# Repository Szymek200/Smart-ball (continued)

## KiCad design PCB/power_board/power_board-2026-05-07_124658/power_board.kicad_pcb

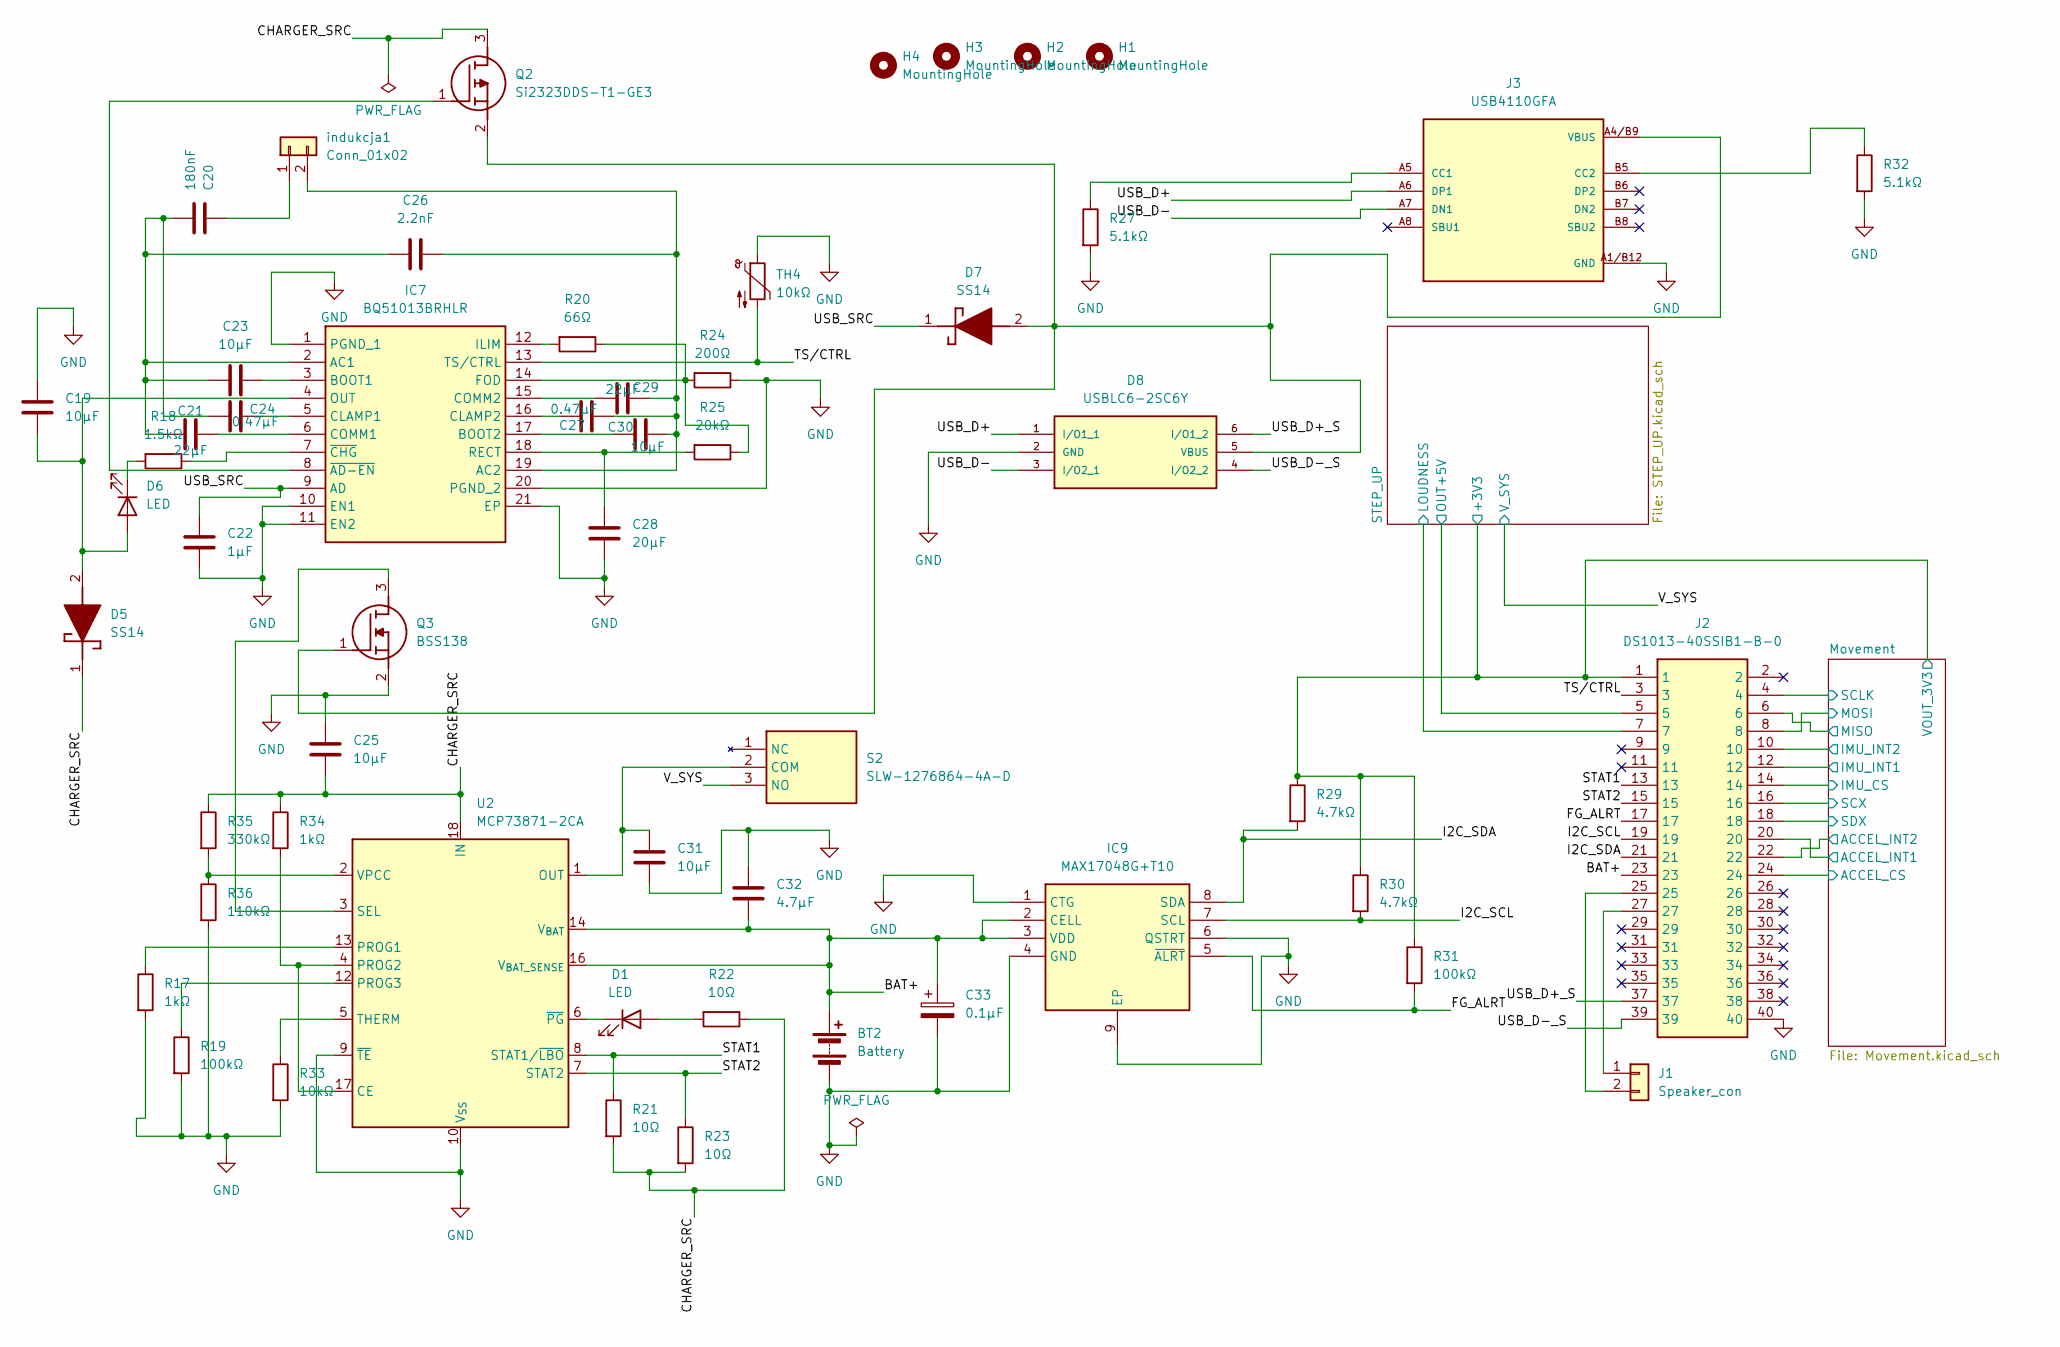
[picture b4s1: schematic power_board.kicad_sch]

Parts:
BT2: Battery; SolderWire-0.75sqmm_1x02_P4.8mm_D1.25mm_OD2.3mm
C19, C23, C25, C30, C31: 10µF; CP_EIA-3216-18_Kemet-A
C20: 180nF; CP_EIA-3216-18_Kemet-A
C21, C29: 22µF; CP_EIA-3216-18_Kemet-A
C22: 1µF; CP_EIA-3216-18_Kemet-A
C24, C27: 0.47µF; CP_EIA-3216-18_Kemet-A
C26: 2.2nF; CP_EIA-3216-18_Kemet-A
C28: 20µF; CP_EIA-3216-18_Kemet-A
C32: 4.7µF; CP_EIA-3216-18_Kemet-A
C33: 0.1µF; CP_EIA-3216-18_Kemet-A
D1, D6: LED; LED_0603_1608Metric
D5, D7: SS14; DIOM5227X270N; Mouser Part Number 512-SS14
D8: USBLC6-2SC6Y; SOT95P280X145-6N; MOUSER_PART_NUMBER 511-USBLC6-2SC6Y
H1, H2, H3, H4: MountingHole; MountingHole_3.2mm_M3_Pad_Via
IC7: BQ51013BRHLR; BQ51050BRHLR; Mouser Part Number 595-BQ51013BRHLR
IC9: MAX17048G+T10; SON50P200X200X80-9N-D; Mouser Part Number 700-MAX17048G+T10
J1: Speaker_con; PinHeader_1x02_P2.54mm_Vertical
J2: DS1013-40SSIB1-B-0; DS101340SSIB1B0; Manufacturer_Part_Number DS1013-40SSIB1-B-0
J3: USB4110GFA; GCT_USB4110GFA
Q2: Si2323DDS-T1-GE3; SOT95P237X112-3N; Mouser Part Number 78-SI2323DDS-T1-GE3
Q3: BSS138; SOT95P240X120-3N; Mouser Part Number 512-BSS138
R17, R34: 1kΩ; R_0603_1608Metric
R18: 1.5kΩ; R_0603_1608Metric
R19, R31: 100kΩ; R_0603_1608Metric
R20: 66Ω; R_0603_1608Metric
R21, R22, R23: 10Ω; R_0603_1608Metric
R24: 200Ω; R_0603_1608Metric
R25: 20kΩ; R_0603_1608Metric
R27, R32: 5.1kΩ; R_0603_1608Metric
R29, R30: 4.7kΩ; R_0603_1608Metric
R33: 10kΩ; R_0603_1608Metric
R35: 330kΩ; R_0603_1608Metric
R36: 110kΩ; R_0603_1608Metric
S2: SLW-1276864-4A-D; SLW12768644AD; Mouser Part Number 179-SLW-1276864-4A-D
TH4: 10kΩ; R_0603_1608Metric
U2: MCP73871-2CA; QFN-20-1EP_4x4mm_P0.5mm_EP2.5x2.5mm
indukcja1: Conn_01x02; PinHeader_1x02_P2.54mm_Vertical

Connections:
/BAT+: BT2.1 (+), C32.2, C33.1, IC9.2 (CELL), IC9.3 (VDD), J2.23, U2.14 (V_{BAT}), U2.15 (V_{BAT}), U2.16 (V_{BAT_SENSE})
/CHARGER_SRC: C25.2, D5.1 (K), Q2.3 (D), R21.2, R22.1, R23.2, R34.1, R35.1, U2.18 (IN), U2.19 (IN)
/FG_ALRT: IC9.5 (~ALRT), J2.17, R31.2
/I2C_SCL: IC9.7 (SCL), J2.19, R30.2
/I2C_SDA: IC9.8 (SDA), J2.21, R29.2
/Movement/ACCEL_CS: J2.24; also elsewhere on the board
/Movement/ACCEL_INT1: J2.20; also elsewhere on the board
/Movement/ACCEL_INT2: J2.22; also elsewhere on the board
/Movement/IMU_CS: J2.14; also elsewhere on the board
/Movement/IMU_INT1: J2.12; also elsewhere on the board
/Movement/IMU_INT2: J2.10; also elsewhere on the board
/Movement/MISO: J2.6; also elsewhere on the board
/Movement/MOSI: J2.8; also elsewhere on the board
/Movement/SCLK: J2.4; also elsewhere on the board
/Movement/SCX: J2.16; also elsewhere on the board
/Movement/SDX: J2.18; also elsewhere on the board
/Movement/VOUT_3V3: J2.1, R29.1, R30.1, R31.1; also elsewhere on the board
/STAT1: J2.13, R21.1, U2.8 (STAT1/~LBO)
/STAT2: J2.15, R23.1, U2.7 (STAT2)
/STEP_UP/LOUDNESS: J2.7; also elsewhere on the board
/STEP_UP/OUT+5V: J2.5; also elsewhere on the board
/TS/CTRL: IC7.13 (TS/CTRL), J2.3, TH4.2
/USB_D+: D8.1 (I/O1_1), J3.A6 (DP1)
/USB_D+_S: D8.6 (I/O1_2), J2.37
/USB_D-: D8.3 (I/O2_1), J3.A7 (DN1)
/USB_D-_S: D8.4 (I/O2_2), J2.39
/USB_SRC: C22.1, D7.1 (K), IC7.9 (AD)
/V_SYS: S2.3 (NO); also elsewhere on the board
GND: BT2.2 (-), C19.2, C22.2, C25.1, C28.2, C31.2, C32.1, C33.2, D8.2 (GND), IC7.1 (PGND_1), IC7.10 (EN1), IC7.11 (EN2), IC7.20 (PGND_2), IC7.21 (EP), IC9.1 (CTG), IC9.4 (GND), IC9.6 (QSTRT), IC9.9 (EP), J2.40, J3.A1/B12 (GND), J3.B1/A12 (GND), J3.S1 (GND), J3.S2 (GND), J3.S3 (GND), J3.S4 (GND), Q3.2 (S), R17.2, R19.2, R24.1, R27.2, R32.2, R33.2, R36.2, TH4.1, U2.9 (~TE), U2.10 (V_{SS}), U2.11 (V_{SS}), U2.21 (V_{SS}); also elsewhere on the board
unnamed: D1.2 (A), R22.2
unnamed: D1.1 (K), U2.6 (~PG)
unnamed: C19.1, D5.2 (A), D6.2 (A), IC7.4 (OUT)
unnamed: D6.1 (K), R18.2
unnamed: C20.2, C21.2, C23.2, C24.2, C26.2, IC7.2 (AC1)
unnamed: C26.1, C27.1, C29.1, C30.1, IC7.19 (AC2), indukcja1.2
unnamed: C23.1, IC7.3 (BOOT1)
unnamed: C30.2, IC7.17 (BOOT2)
unnamed: C24.1, IC7.5 (CLAMP1)
unnamed: C27.2, IC7.16 (CLAMP2)
unnamed: C21.1, IC7.6 (COMM1)
unnamed: C29.2, IC7.15 (COMM2)
unnamed: IC7.14 (FOD), R20.1, R24.2, R25.1
unnamed: IC7.12 (ILIM), R20.2
unnamed: C28.1, IC7.18 (RECT), R25.2
unnamed: IC7.8 (~AD-EN), Q2.1 (G)
unnamed: IC7.7 (~CHG), R18.1
unnamed: J1.1, J2.27
unnamed: J1.2, J2.25
unnamed: J3.A5 (CC1), R27.1
unnamed: J3.B5 (CC2), R32.1
unnamed: Q3.3 (D), U2.3 (SEL)
unnamed: C31.1, S2.2 (COM), U2.1 (OUT), U2.20 (OUT)
unnamed: R34.2, U2.4 (PROG2), U2.17 (CE)
unnamed: R17.1, U2.13 (PROG1)
unnamed: R19.1, U2.12 (PROG3)
unnamed: R33.1, U2.5 (THERM)
unnamed: R35.2, R36.1, U2.2 (VPCC)
unnamed: C20.1, indukcja1.1
VBUS: D7.2 (A), D8.5 (VBUS), J3.A4/B9 (VBUS), J3.B4/A9 (VBUS), Q2.2 (S), Q3.1 (G)

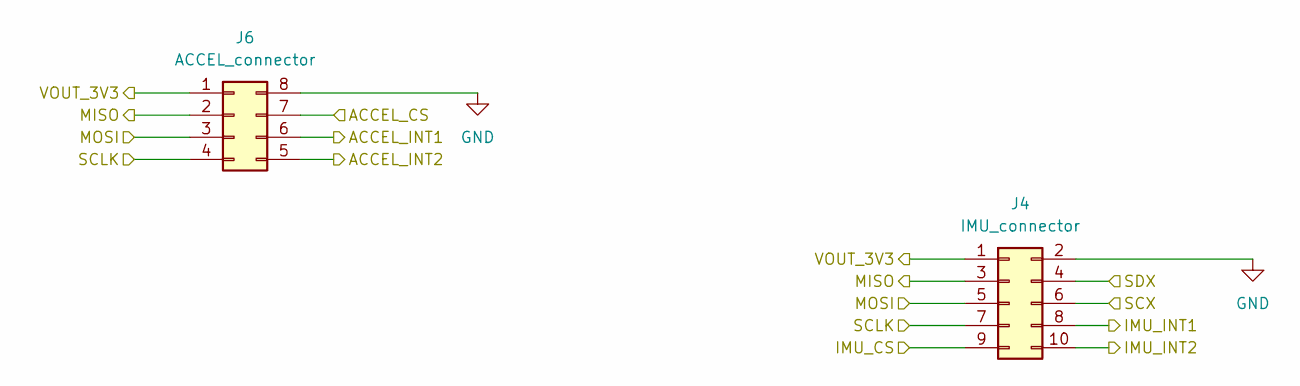
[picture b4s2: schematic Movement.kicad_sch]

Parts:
J4: IMU_connector; PinHeader_2x05_P2.54mm_Vertical
J6: ACCEL_connector; PinHeader_2x04_P2.54mm_Vertical

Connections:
/Movement/ACCEL_CS: J6.7; also elsewhere on the board
/Movement/ACCEL_INT1: J6.6; also elsewhere on the board
/Movement/ACCEL_INT2: J6.5; also elsewhere on the board
/Movement/IMU_CS: J4.9; also elsewhere on the board
/Movement/IMU_INT1: J4.8; also elsewhere on the board
/Movement/IMU_INT2: J4.10; also elsewhere on the board
/Movement/MISO: J4.3, J6.2; also elsewhere on the board
/Movement/MOSI: J4.5, J6.3; also elsewhere on the board
/Movement/SCLK: J4.7, J6.4; also elsewhere on the board
/Movement/SCX: J4.6; also elsewhere on the board
/Movement/SDX: J4.4; also elsewhere on the board
/Movement/VOUT_3V3: J4.1, J6.1; also elsewhere on the board
GND: J4.2, J6.8; also elsewhere on the board

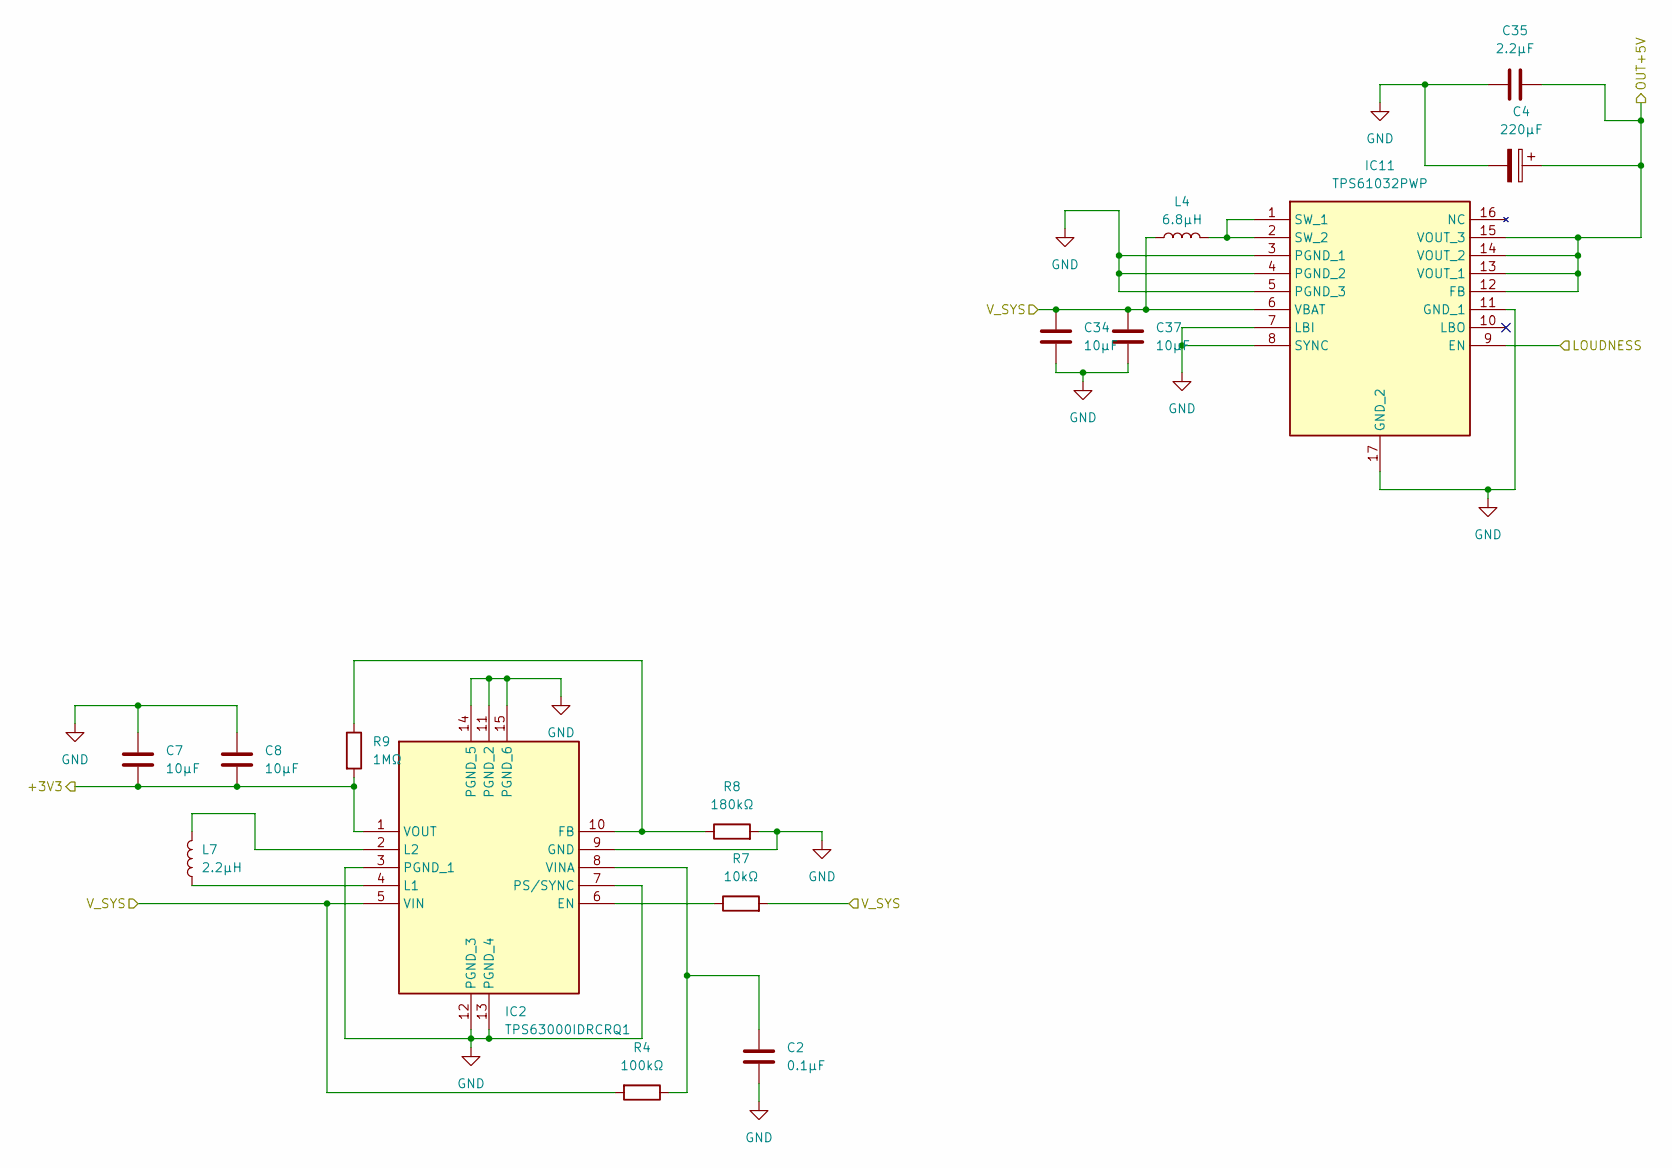
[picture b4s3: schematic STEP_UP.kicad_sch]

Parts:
C2: 0.1μF; CP_Elec_6.3x5.4
C4: 220µF; CP_Elec_6.3x5.4
C7, C8: 10μF; CP_Elec_6.3x5.4
C34, C37: 10µF; CP_Elec_6.3x5.4
C35: 2.2µF; CP_Elec_6.3x5.4
IC2: TPS63000IDRCRQ1; Mouser Part Number 595-TPS63000IDRCRQ1
IC11: TPS61032PWP; SOP65P640X120-17N; Mouser Part Number 595-TPS61032PWP
L4: 6.8µH; L_6.3x6.3_H3
L7: 2.2µH; L_6.3x6.3_H3
R4: 100kΩ; R_0603_1608Metric
R7: 10kΩ; R_0603_1608Metric
R8: 180kΩ; R_0603_1608Metric
R9: 1MΩ; R_0603_1608Metric

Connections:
/Movement/VOUT_3V3: C7.2, C8.2, IC2.1 (VOUT), R9.2; also elsewhere on the board
/STEP_UP/LOUDNESS: IC11.9 (EN); also elsewhere on the board
/STEP_UP/OUT+5V: C4.1, C35.2, IC11.12 (FB), IC11.13 (VOUT_1), IC11.14 (VOUT_2), IC11.15 (VOUT_3); also elsewhere on the board
/V_SYS: C34.1, C37.1, IC2.5 (VIN), IC11.6 (VBAT), L4.1, R4.2, R7.2; also elsewhere on the board
GND: C2.2, C4.2, C7.1, C8.1, C34.2, C35.1, C37.2, IC2.3 (PGND_1), IC2.7 (PS/SYNC), IC2.9 (GND), IC2.11 (PGND_2), IC2.12 (PGND_3), IC2.13 (PGND_4), IC2.14 (PGND_5), IC2.15 (PGND_6), IC11.3 (PGND_1), IC11.4 (PGND_2), IC11.5 (PGND_3), IC11.7 (LBI), IC11.8 (SYNC), IC11.11 (GND_1), IC11.17 (GND_2), R8.2; also elsewhere on the board
unnamed: IC2.6 (EN), R7.1
unnamed: IC2.10 (FB), R8.1, R9.1
unnamed: IC2.4 (L1), L7.1
unnamed: IC2.2 (L2), L7.2
unnamed: C2.1, IC2.8 (VINA), R4.1
unnamed: IC11.1 (SW_1), IC11.2 (SW_2), L4.2

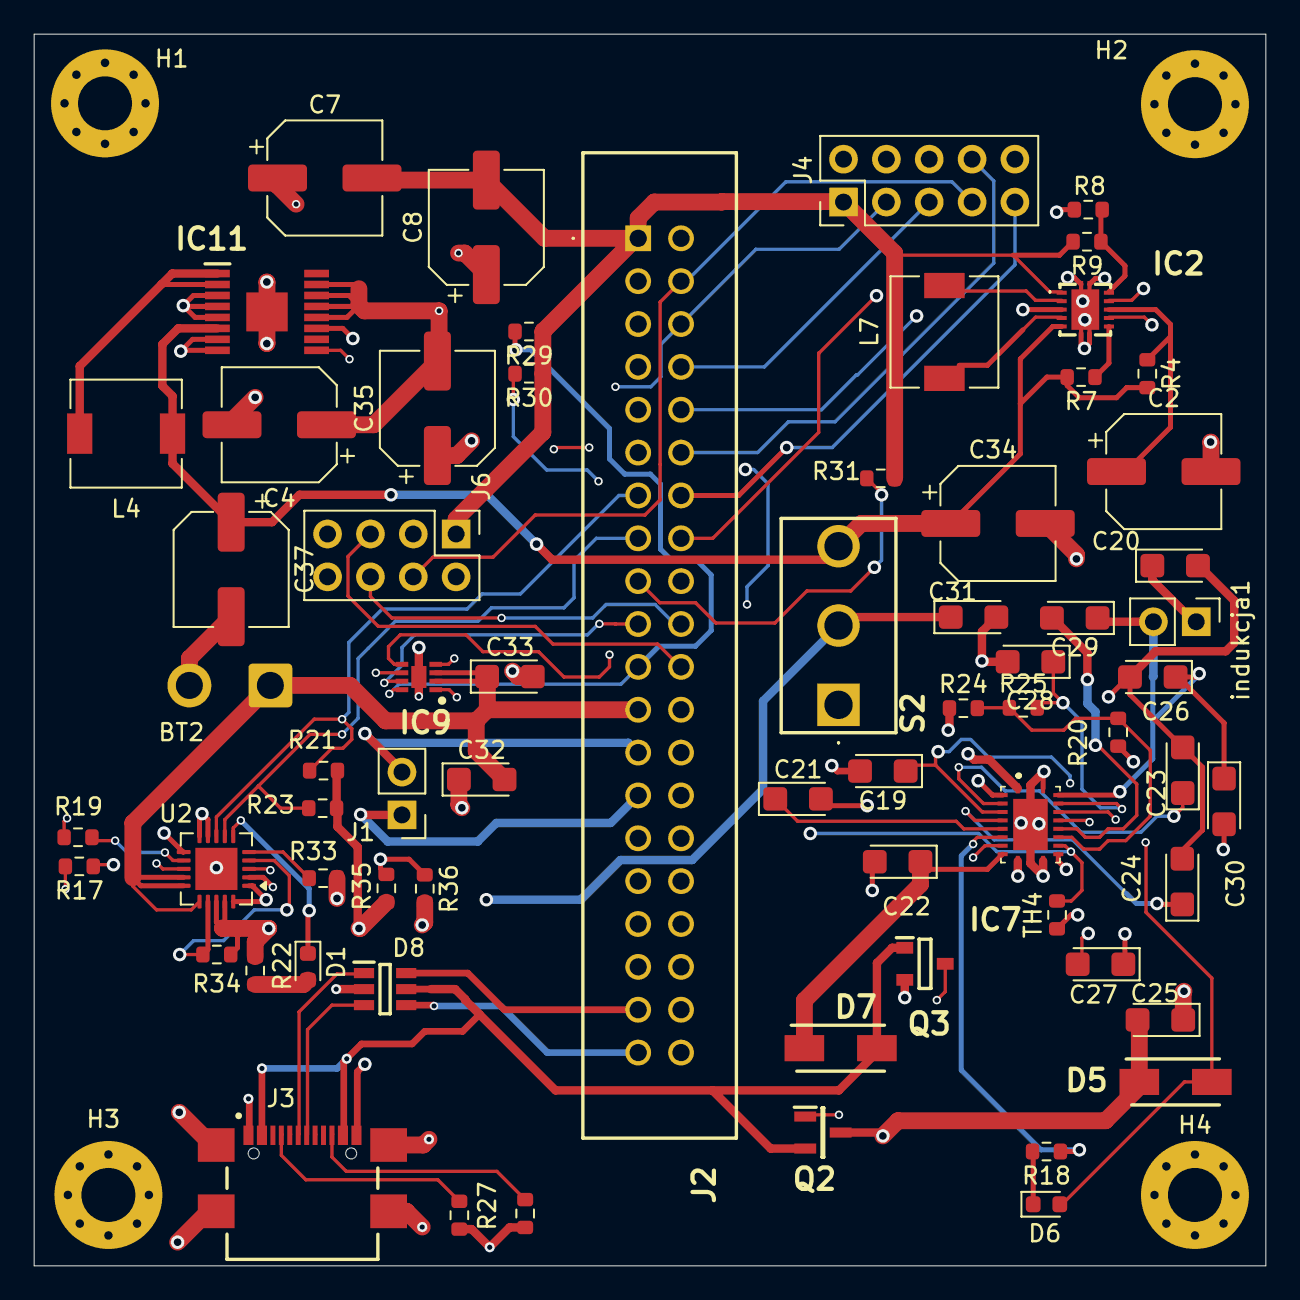
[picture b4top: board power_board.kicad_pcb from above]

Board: 4 copper layers, 73.0 x 73.0 mm, 71 parts (0 on the bottom side), 65 nets.

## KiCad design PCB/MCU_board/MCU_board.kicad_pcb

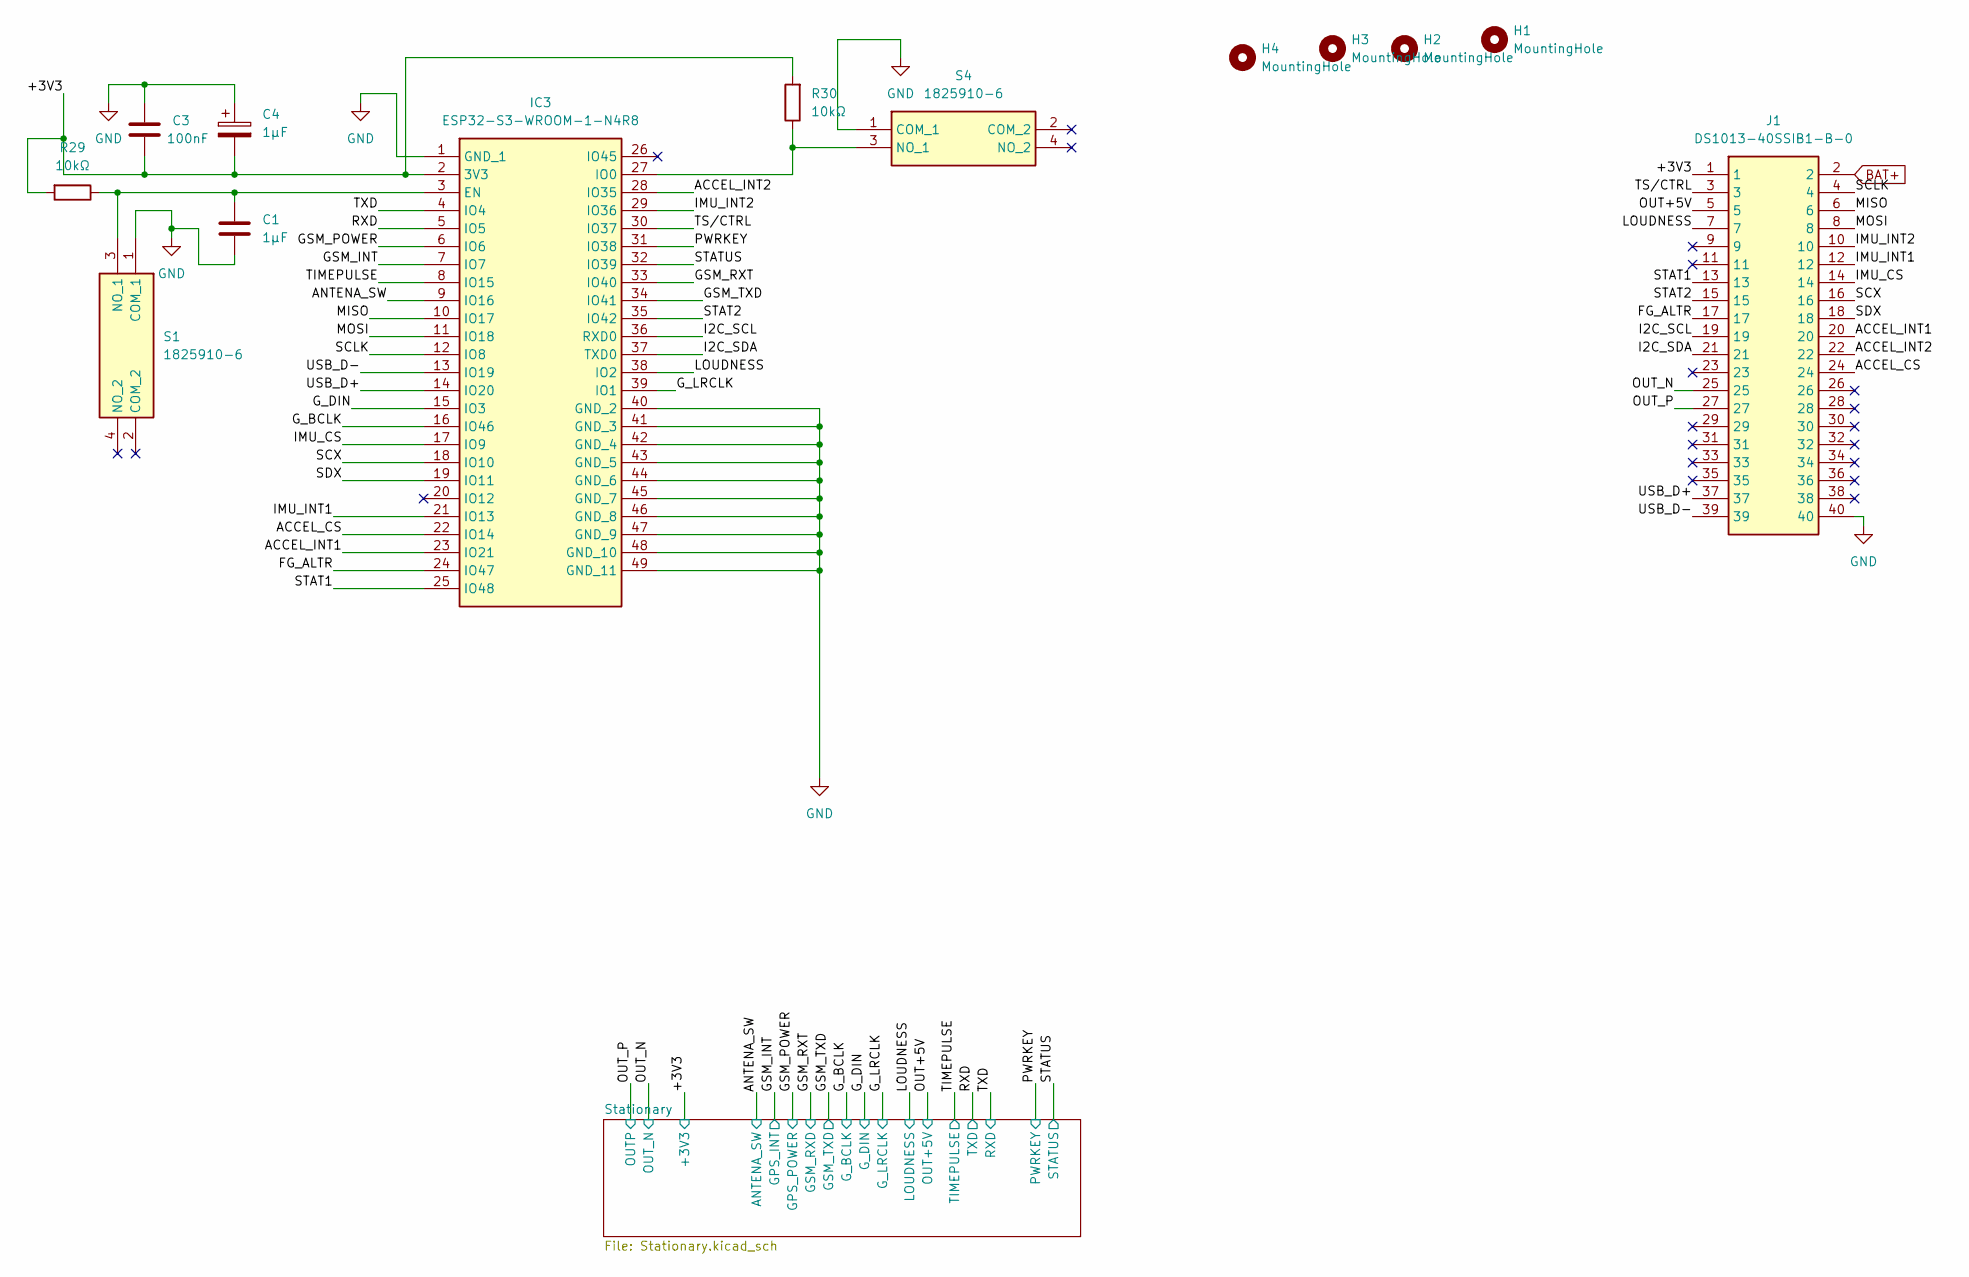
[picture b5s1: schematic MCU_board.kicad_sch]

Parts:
C1: 1μF; CP_Elec_6.3x5.4
C3: 100nF; CP_Elec_6.3x5.4
C4: 1μF; CP_EIA-3216-18_Kemet-A
H1, H2, H3, H4: MountingHole; MountingHole_3.2mm_M3_Pad_Via
IC3: ESP32-S3-WROOM-1-N4R8; ESP32S3WROOM1N4R8; Mouser Part Number 356-ESP32S3WROM1N4R8
J1: DS1013-40SSIB1-B-0; DS101340SSIB1B0; Manufacturer_Part_Number DS1013-40SSIB1-B-0
R29, R30: 10kΩ; R_0603_1608Metric
S1, S4: 1825910-6; 18259106; Manufacturer_Part_Number 1825910-6

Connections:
/+3V3: C3.2, C4.2, IC3.2 (3V3), J1.1, R29.2, R30.2; also elsewhere on the board
/ACCEL_CS: IC3.22 (IO14), J1.24
/ACCEL_INT1: IC3.23 (IO21), J1.20
/ACCEL_INT2: IC3.28 (IO35), J1.22
/ANTENA_SW: IC3.9 (IO16); also elsewhere on the board
/FG_ALTR: IC3.24 (IO47), J1.17
/GSM_INT: IC3.7 (IO7); also elsewhere on the board
/GSM_POWER: IC3.6 (IO6); also elsewhere on the board
/GSM_RXT: IC3.33 (IO40); also elsewhere on the board
/GSM_TXD: IC3.34 (IO41); also elsewhere on the board
/G_BCLK: IC3.16 (IO46); also elsewhere on the board
/G_DIN: IC3.15 (IO3); also elsewhere on the board
/G_LRCLK: IC3.39 (IO1); also elsewhere on the board
/I2C_SCL: IC3.36 (RXD0), J1.19
/I2C_SDA: IC3.37 (TXD0), J1.21
/IMU_CS: IC3.17 (IO9), J1.14
/IMU_INT1: IC3.21 (IO13), J1.12
/IMU_INT2: IC3.29 (IO36), J1.10
/LOUDNESS: IC3.38 (IO2), J1.7; also elsewhere on the board
/MISO: IC3.10 (IO17), J1.6
/MOSI: IC3.11 (IO18), J1.8
/OUT+5V: J1.5; also elsewhere on the board
/OUT_N: J1.25; also elsewhere on the board
/OUT_P: J1.27; also elsewhere on the board
/PWRKEY: IC3.31 (IO38); also elsewhere on the board
/RXD: IC3.5 (IO5); also elsewhere on the board
/SCLK: IC3.12 (IO8), J1.4
/SCX: IC3.18 (IO10), J1.16
/SDX: IC3.19 (IO11), J1.18
/STAT1: IC3.25 (IO48), J1.13
/STAT2: IC3.35 (IO42), J1.15
/STATUS: IC3.32 (IO39); also elsewhere on the board
/TIMEPULSE: IC3.8 (IO15); also elsewhere on the board
/TS/CTRL: IC3.30 (IO37), J1.3
/TXD: IC3.4 (IO4); also elsewhere on the board
/USB_D+: IC3.14 (IO20), J1.37
/USB_D-: IC3.13 (IO19), J1.39
BAT+: J1.2; also elsewhere on the board
GND: C1.2, C3.1, C4.1, IC3.1 (GND_1), IC3.40 (GND_2), IC3.41 (GND_3), IC3.42 (GND_4), IC3.43 (GND_5), IC3.44 (GND_6), IC3.45 (GND_7), IC3.46 (GND_8), IC3.47 (GND_9), IC3.48 (GND_10), IC3.49 (GND_11), J1.40, S1.1 (COM_1), S4.1 (COM_1); also elsewhere on the board
unnamed: C1.1, IC3.3 (EN), R29.1, S1.3 (NO_1)
unnamed: IC3.27 (IO0), R30.1, S4.3 (NO_1)

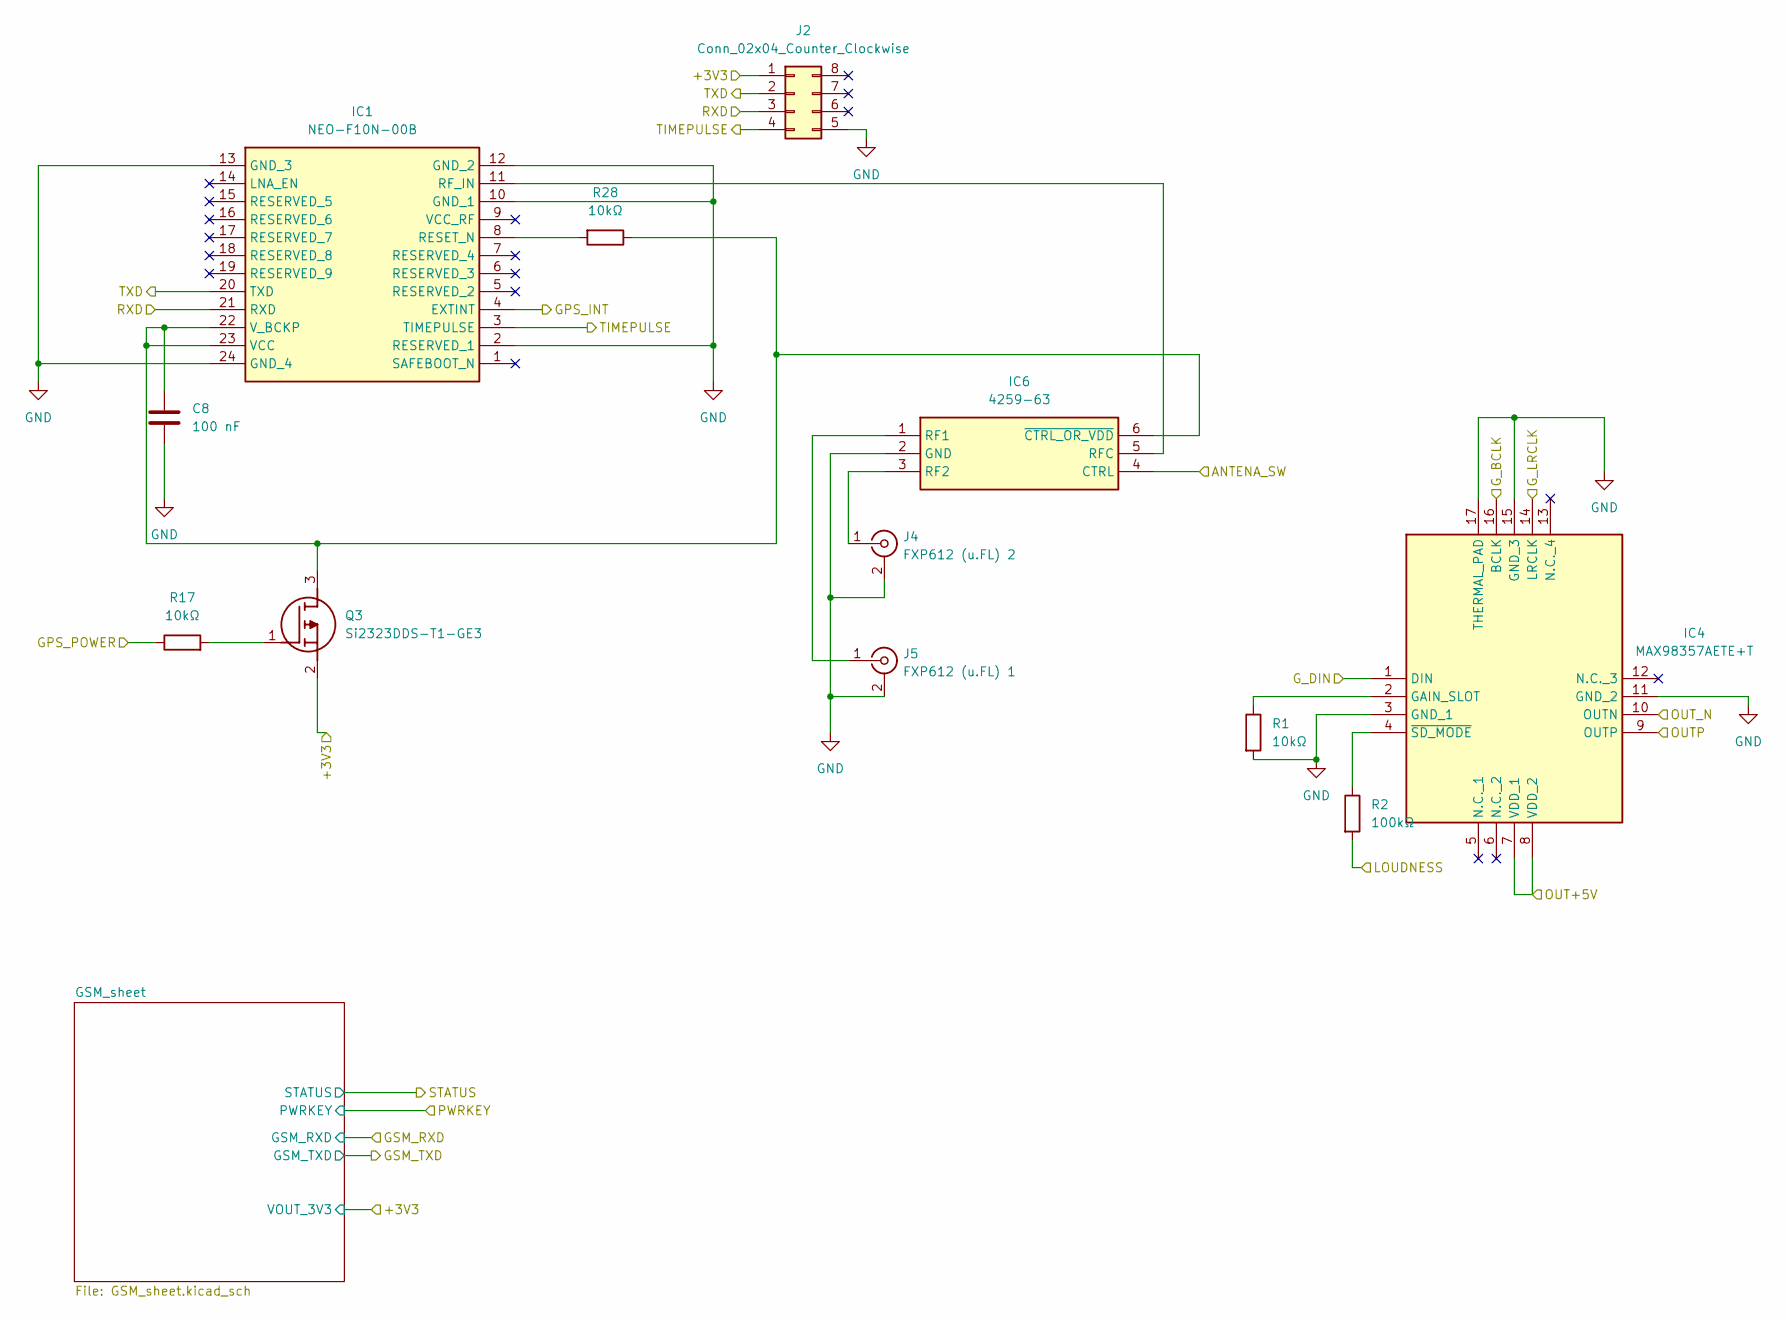
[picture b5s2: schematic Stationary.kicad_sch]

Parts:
C8: 100 nF; CP_Elec_6.3x5.4
IC1: NEO-F10N-00B; NEOF10N00B; Mouser Part Number 377-NEO-F10N-00B
IC4: MAX98357AETE+T; QFN50P300X300X80-17N; Mouser Part Number 700-MAX98357AETE+T
IC6: 4259-63; SOT65P210X110-6N; Mouser Part Number 81-4259-63
J2: Conn_02x04_Counter_Clockwise; PinHeader_2x04_P2.54mm_Vertical
J4: FXP612 (u.FL) 2; U.FL_Molex_MCRF_73412-0110_Vertical
J5: FXP612 (u.FL) 1; U.FL_Molex_MCRF_73412-0110_Vertical
Q3: Si2323DDS-T1-GE3; SOT-23; Mouser Part Number 78-SI2323DDS-T1-GE3
R1, R17, R28: 10kΩ; R_0603_1608Metric
R2: 100kΩ; R_0603_1608Metric

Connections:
/+3V3: J2.1, Q3.2 (S); also elsewhere on the board
/ANTENA_SW: IC6.4 (CTRL); also elsewhere on the board
/GSM_INT: IC1.4 (EXTINT); also elsewhere on the board
/GSM_POWER: R17.1; also elsewhere on the board
/G_BCLK: IC4.16 (BCLK); also elsewhere on the board
/G_DIN: IC4.1 (DIN); also elsewhere on the board
/G_LRCLK: IC4.14 (LRCLK); also elsewhere on the board
/LOUDNESS: R2.2; also elsewhere on the board
/OUT+5V: IC4.7 (VDD_1), IC4.8 (VDD_2); also elsewhere on the board
/OUT_N: IC4.10 (OUTN); also elsewhere on the board
/OUT_P: IC4.9 (OUTP); also elsewhere on the board
/RXD: IC1.20 (TXD), J2.2; also elsewhere on the board
/TIMEPULSE: IC1.3 (TIMEPULSE), J2.4; also elsewhere on the board
/TXD: IC1.21 (RXD), J2.3; also elsewhere on the board
GND: C8.2, IC1.2 (RESERVED_1), IC1.10 (GND_1), IC1.12 (GND_2), IC1.13 (GND_3), IC1.24 (GND_4), IC4.3 (GND_1), IC4.11 (GND_2), IC4.15 (GND_3), IC4.17 (THERMAL_PAD), IC6.2 (GND), J2.5, J4.2 (Ext), J5.2 (Ext), R1.2; also elsewhere on the board
unnamed: IC1.8 (RESET_N), R28.2
unnamed: IC1.11 (RF_IN), IC6.5 (RFC)
unnamed: C8.1, IC1.22 (V_BCKP), IC1.23 (VCC), IC6.6 (~CTRL_OR_VDD), Q3.3 (D), R28.1
unnamed: IC4.2 (GAIN_SLOT), R1.1
unnamed: IC4.4 (~SD_MODE), R2.1
unnamed: IC6.1 (RF1), J5.1 (In)
unnamed: IC6.3 (RF2), J4.1 (In)
unnamed: Q3.1 (G), R17.2

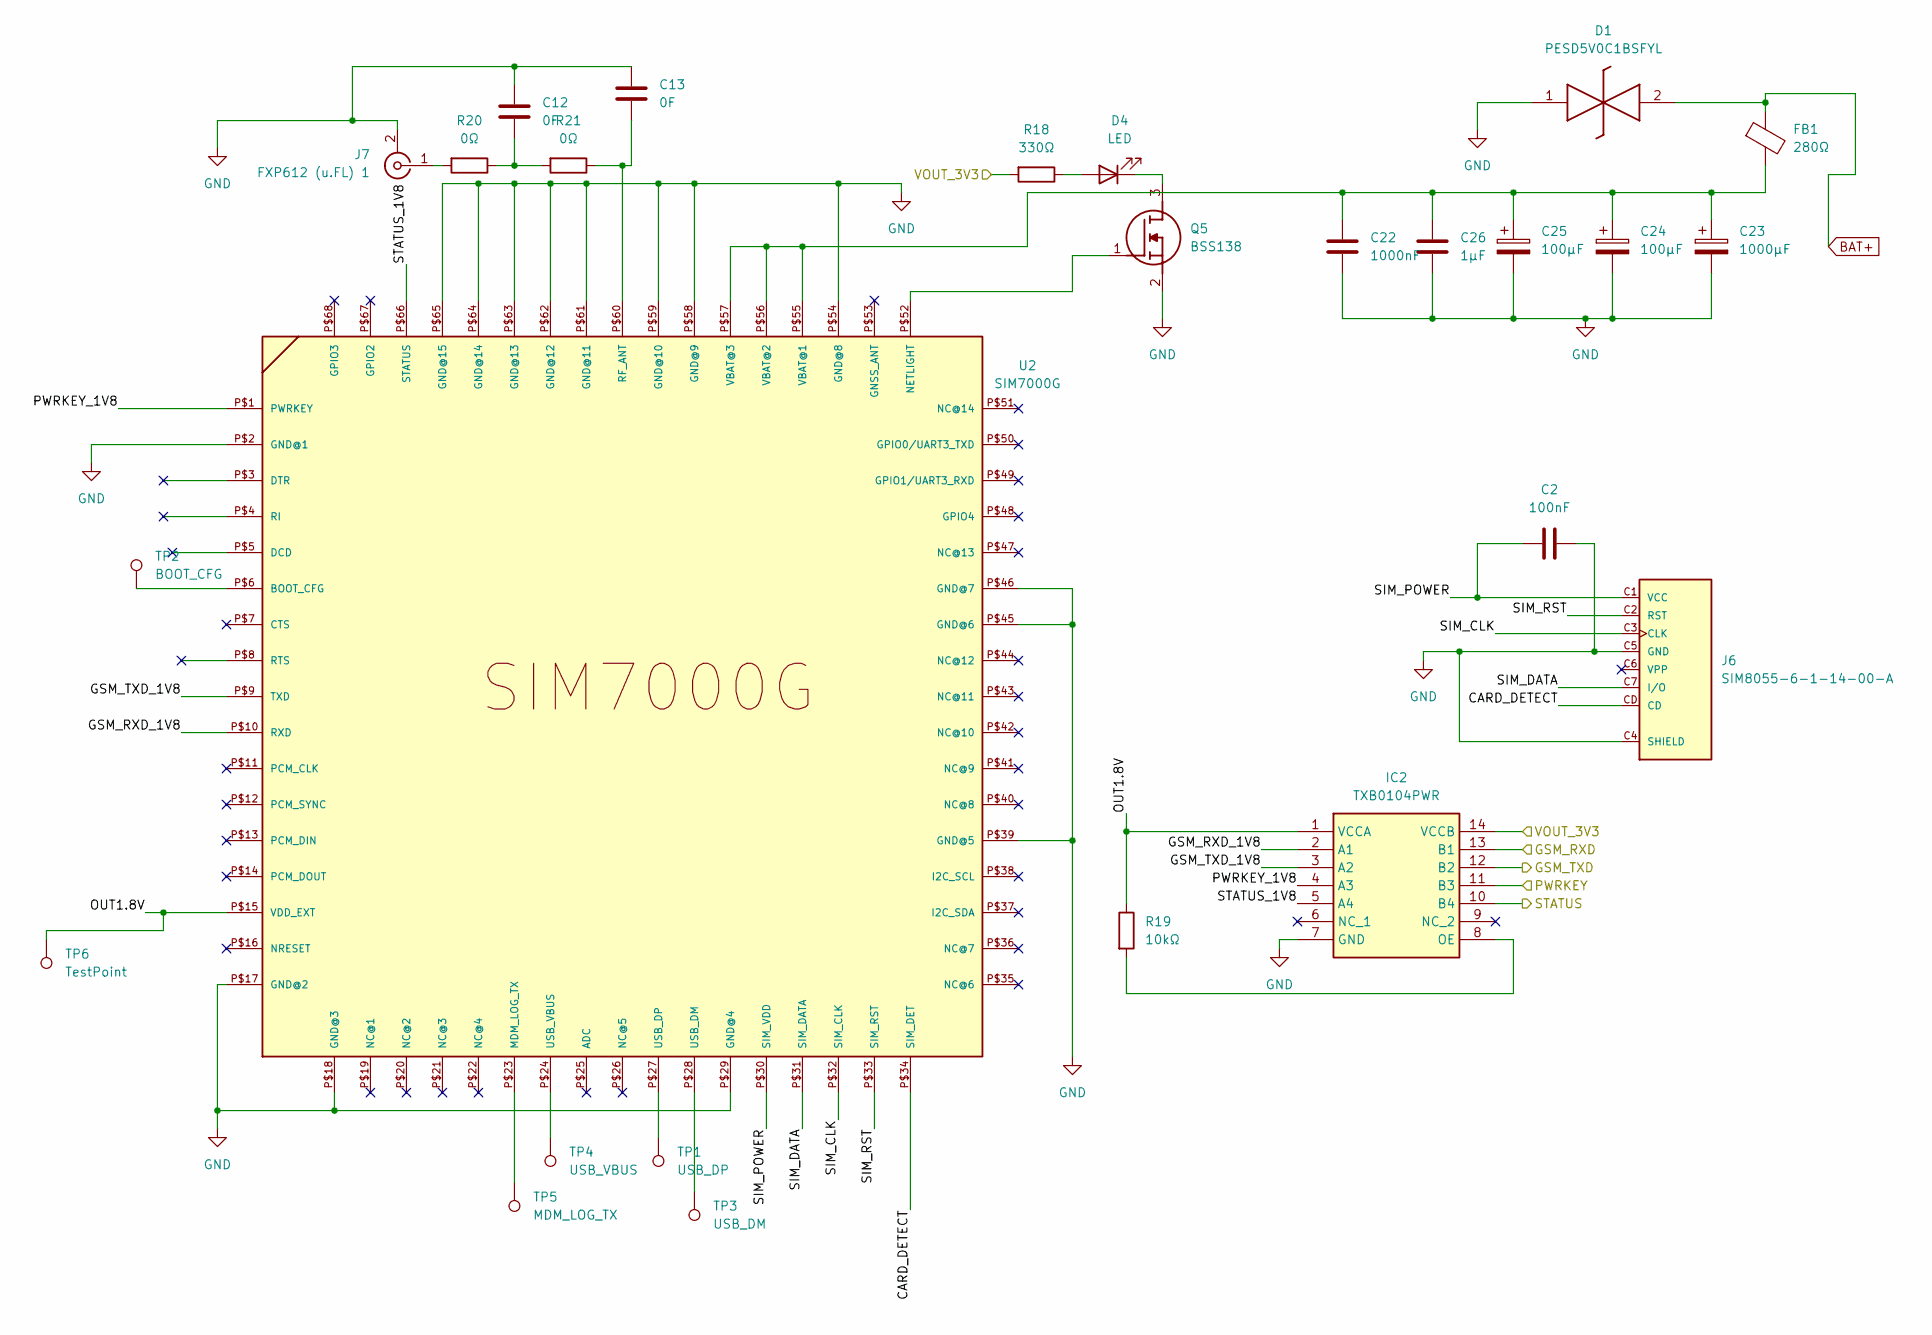
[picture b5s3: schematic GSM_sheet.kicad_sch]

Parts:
C2: 100nF; CP_Elec_6.3x5.4
C12, C13: 0F; CP_Elec_6.3x5.4
C22: 1000nF; CP_Elec_6.3x5.4
C23: 1000µF; CP_EIA-3216-18_Kemet-A
C24, C25: 100µF; CP_EIA-3216-18_Kemet-A
C26: 1µF; CP_Elec_6.3x5.4
D1: PESD5V0C1BSFYL; PMEG3005AESFYL; Mouser Part Number 771-PESD5V0C1BSFYL
D4: LED; LED_0603_1608Metric
FB1: 280Ω; L_0805_2012Metric_Pad1.05x1.20mm_HandSolder
IC2: TXB0104PWR; SOP65P640X120-14N; Mouser Part Number 595-TXB0104PWR
J6: SIM8055-6-1-14-00-A; GCT_SIM8055-6-1-14-00-A; PARTREV A1
J7: FXP612 (u.FL) 1; U.FL_Molex_MCRF_73412-0110_Vertical
Q5: BSS138; SOT95P240X120-3N; Mouser Part Number 512-BSS138
R18: 330Ω; R_0603_1608Metric
R19: 10kΩ; R_0603_1608Metric
R20, R21: 0Ω; R_0603_1608Metric
TP1: USB_DP; TestPoint_THTPad_D2.0mm_Drill1.0mm
TP2: BOOT_CFG; TestPoint_THTPad_D2.0mm_Drill1.0mm
TP3: USB_DM; TestPoint_THTPad_D2.0mm_Drill1.0mm
TP4: USB_VBUS; TestPoint_THTPad_D2.0mm_Drill1.0mm
TP5: MDM_LOG_TX; TestPoint_THTPad_D2.0mm_Drill1.0mm
TP6: TestPoint; TestPoint_THTPad_D2.0mm_Drill1.0mm
U2: SIM7000G

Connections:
/+3V3: IC2.14 (VCCB), R18.2; also elsewhere on the board
/GSM_RXT: IC2.13 (B1); also elsewhere on the board
/GSM_TXD: IC2.12 (B2); also elsewhere on the board
/PWRKEY: IC2.11 (B3); also elsewhere on the board
/STATUS: IC2.10 (B4); also elsewhere on the board
/Stationary/GSM_sheet/CARD_DETECT: J6.CD, U2.P$34 (SIM_DET)
/Stationary/GSM_sheet/GSM_RXD_1V8: IC2.2 (A1), U2.P$10 (RXD)
/Stationary/GSM_sheet/GSM_TXD_1V8: IC2.3 (A2), U2.P$9 (TXD)
/Stationary/GSM_sheet/OUT1.8V: IC2.1 (VCCA), R19.1, TP6.1 (1_1), U2.P$15 (VDD_EXT)
/Stationary/GSM_sheet/PWRKEY_1V8: IC2.4 (A3), U2.P$1 (PWRKEY)
/Stationary/GSM_sheet/SIM_CLK: J6.C3 (CLK), U2.P$32 (SIM_CLK)
/Stationary/GSM_sheet/SIM_DATA: J6.C7 (I/O), U2.P$31 (SIM_DATA)
/Stationary/GSM_sheet/SIM_POWER: C2.2, J6.C1 (VCC), U2.P$30 (SIM_VDD)
/Stationary/GSM_sheet/SIM_RST: J6.C2 (RST), U2.P$33 (SIM_RST)
/Stationary/GSM_sheet/STATUS_1V8: IC2.5 (A4), U2.P$66 (STATUS)
BAT+: D1.2 (K2), FB1.1; also elsewhere on the board
GND: C2.1, C12.1, C13.1, C22.2, C23.2, C24.2, C25.2, C26.2, D1.1 (K1), IC2.7 (GND), J6.C4 (SHIELD), J6.C5 (GND), J6.C8 (SHIELD), J7.2 (Ext), Q5.2 (S), U2.P$2 (GND@1), U2.P$17 (GND@2), U2.P$18 (GND@3), U2.P$29 (GND@4), U2.P$39 (GND@5), U2.P$45 (GND@6), U2.P$46 (GND@7), U2.P$54 (GND@8), U2.P$58 (GND@9), U2.P$59 (GND@10), U2.P$61 (GND@11), U2.P$62 (GND@12), U2.P$63 (GND@13), U2.P$64 (GND@14), U2.P$65 (GND@15); also elsewhere on the board
unnamed: C12.2, R20.1, R21.2
unnamed: D4.2 (A), R18.1
unnamed: D4.1 (K), Q5.3 (D)
unnamed: IC2.8 (OE), R19.2
unnamed: J7.1 (In), R20.2
unnamed: Q5.1 (G), U2.P$52 (NETLIGHT)
unnamed: TP2.1 (1_1), U2.P$6 (BOOT_CFG)
unnamed: TP5.1 (1_1), U2.P$23 (MDM_LOG_TX)
unnamed: C13.2, R21.1, U2.P$60 (RF_ANT)
unnamed: TP3.1 (1_1), U2.P$28 (USB_DM)
unnamed: TP1.1 (1_1), U2.P$27 (USB_DP)
unnamed: TP4.1 (1_1), U2.P$24 (USB_VBUS)
unnamed: C22.1, C23.1, C24.1, C25.1, C26.1, FB1.2, U2.P$55 (VBAT@1), U2.P$56 (VBAT@2), U2.P$57 (VBAT@3)
